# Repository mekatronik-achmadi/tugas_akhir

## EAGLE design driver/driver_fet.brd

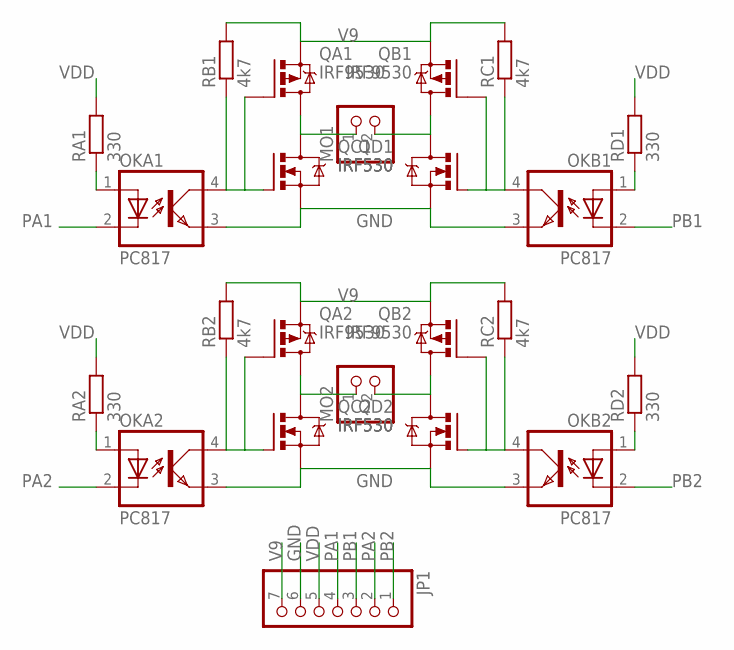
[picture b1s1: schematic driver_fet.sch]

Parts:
JP1: PINHD-1X7; 1X07
MO1, MO2: PINHD-1X2; 1X02
OKA1, OKA2: PC817; DIL04
OKB1, OKB2: PC817; DIL04
QA1, QA2: IRF9530; TO220BV
QB1, QB2: IRF9530; TO220BV
QC1, QC2: IRF530; TO220BV
QD1, QD2: IRF530; TO220BV
RA1, RA2: 330; R1206
RB1, RB2: 4k7; R1206
RC1, RC2: 4k7; R1206
RD1, RD2: 330; R1206

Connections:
GND: JP1.6, OKA1.3 (EMIT), OKA2.3 (EMIT), OKB1.3 (EMIT), OKB2.3 (EMIT), QC1.S, QC2.S, QD1.S, QD2.S
unnamed: MO1.1, QA1.D, QC1.D
unnamed: MO1.2, QB1.D, QD1.D
unnamed: MO2.1, QA2.D, QC2.D
unnamed: MO2.2, QB2.D, QD2.D
unnamed: OKA1.4 (COL), QA1.G, QC1.G, RB1.1
unnamed: OKB1.4 (COL), QB1.G, QD1.G, RC1.1
unnamed: OKA2.4 (COL), QA2.G, QC2.G, RB2.1
unnamed: OKA1.1 (A), RA1.1
unnamed: OKB1.1 (A), RD1.1
unnamed: OKB2.4 (COL), QB2.G, QD2.G, RC2.1
unnamed: OKA2.1 (A), RA2.1
unnamed: OKB2.1 (A), RD2.1
PA1: JP1.4, OKA1.2 (C)
PA2: JP1.2, OKA2.2 (C)
PB1: JP1.3, OKB1.2 (C)
PB2: JP1.1, OKB2.2 (C)
V9: JP1.7, QA1.S, QA2.S, QB1.S, QB2.S, RB1.2, RB2.2, RC1.2, RC2.2
VDD: JP1.5, RA1.2, RA2.2, RD1.2, RD2.2

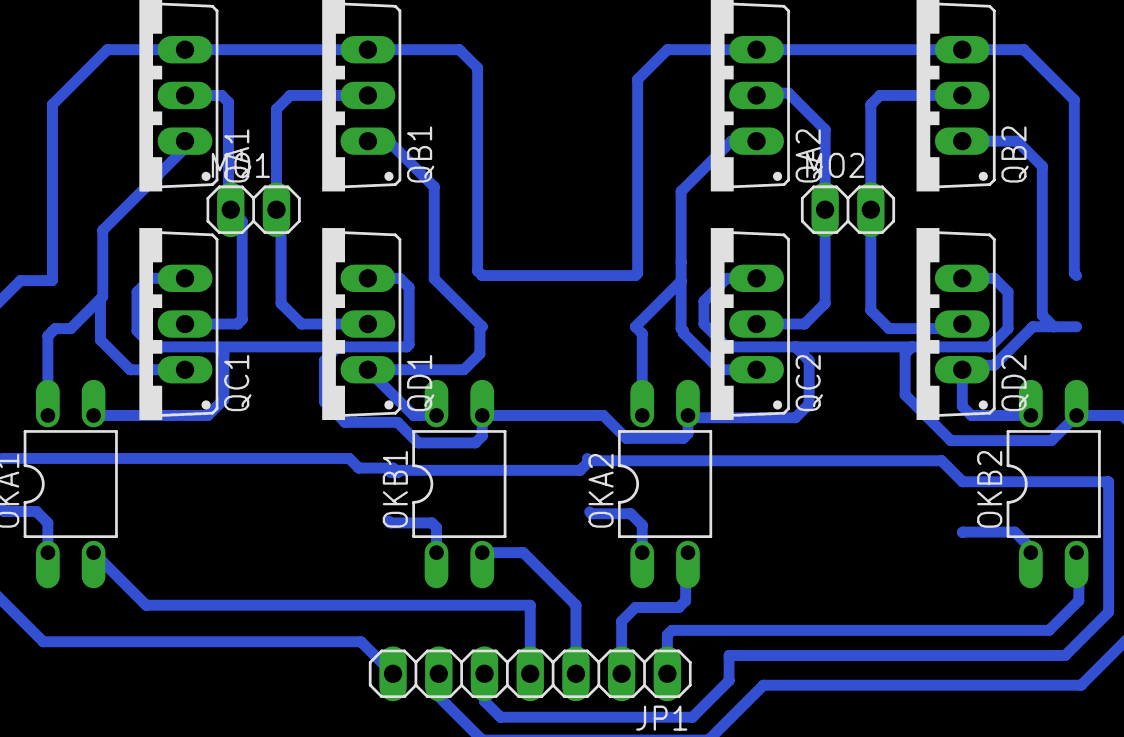
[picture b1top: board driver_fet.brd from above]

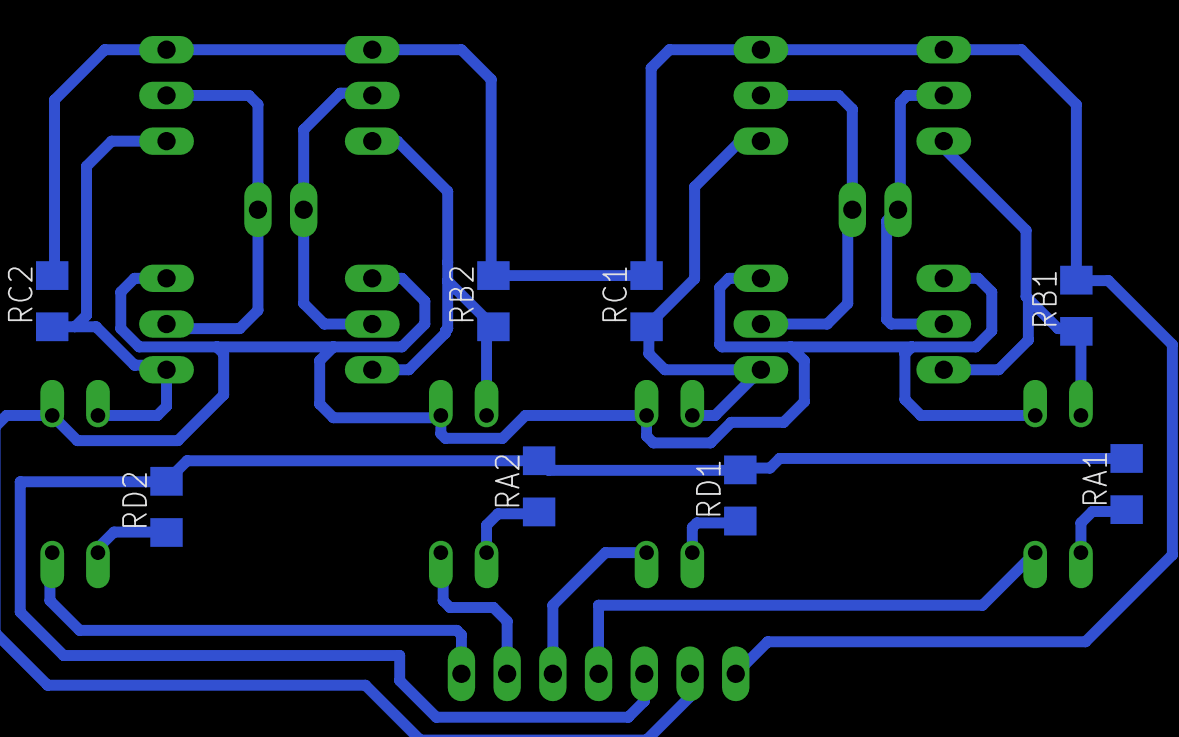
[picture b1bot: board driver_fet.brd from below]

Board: 2 copper layers, 23 parts (8 on the bottom side), 19 nets.

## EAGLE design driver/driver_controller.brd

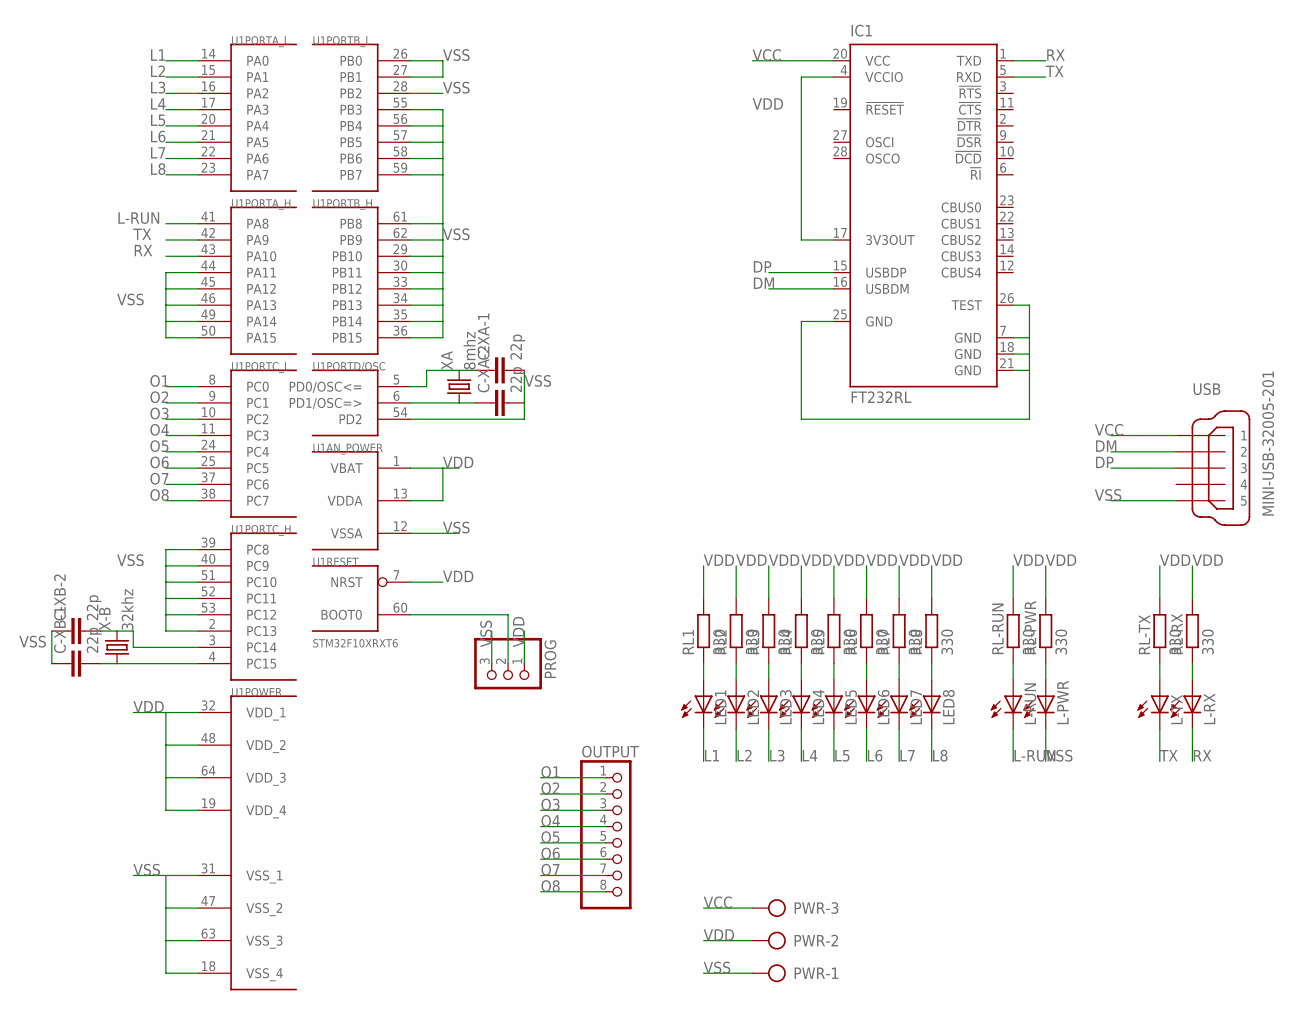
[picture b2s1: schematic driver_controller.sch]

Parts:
C-XA-1, C-XA-2: 22p; C1206
C-XB-1, C-XB-2: 22p; C1206
IC1: FT232RL; SSOP28
L-PWR: LEDSML1206; SML1206
L-RUN: LEDSML1206; SML1206
L-RX: LEDSML1206; SML1206
L-TX: LEDSML1206; SML1206
LED1, LED2, LED3, LED4, LED5, LED6, LED7, LED8: LEDSML1206; SML1206
OUTPUT: PINHD-1X8; 1X08
PROG: PINHD-1X3; 1X03
PWR: AK300/3
RL1, RL2, RL3, RL4, RL5, RL6, RL7, RL8: 330; R1206
RL-PWR: 330; R1206
RL-RUN: 330; R1206
RL-RX: 330; R1206
RL-TX: 330; R1206
U1: STM32F10XRXT6; TQFP64
USB: MINI-USB-32005-201; 32005-201
X-B: 32khz; TC26V
XA: 8mhz; HC49/S

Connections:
DM: IC1.16 (USBDM), USB.2
DP: IC1.15 (USBDP), USB.3
L1: LED1.C, U1.14 (PA0)
L2: LED2.C, U1.15 (PA1)
L3: LED3.C, U1.16 (PA2)
L4: LED4.C, U1.17 (PA3)
L5: LED5.C, U1.20 (PA4)
L6: LED6.C, U1.21 (PA5)
L7: LED7.C, U1.22 (PA6)
L8: LED8.C, U1.23 (PA7)
L-RUN: L-RUN.C, U1.41 (PA8)
unnamed: PROG.2, U1.60 (BOOT0)
unnamed: C-XB-1.2, U1.4 (PC15), X-B.1
unnamed: C-XB-2.2, U1.3 (PC14), X-B.2
unnamed: LED1.A, RL1.1
unnamed: C-XA-2.1, U1.6 (PD1/OSC=>), XA.1
unnamed: C-XA-1.1, U1.5 (PD0/OSC<=), XA.2
unnamed: LED2.A, RL2.1
unnamed: L-PWR.A, RL-PWR.1
unnamed: LED3.A, RL3.1
unnamed: LED4.A, RL4.1
unnamed: LED5.A, RL5.1
unnamed: LED6.A, RL6.1
unnamed: LED7.A, RL7.1
unnamed: LED8.A, RL8.1
unnamed: L-RUN.A, RL-RUN.1
unnamed: L-TX.A, RL-TX.1
unnamed: L-RX.A, RL-RX.1
O1: OUTPUT.1, U1.8 (PC0)
O2: OUTPUT.2, U1.9 (PC1)
O3: OUTPUT.3, U1.10 (PC2)
O4: OUTPUT.4, U1.11 (PC3)
O5: OUTPUT.5, U1.24 (PC4)
O6: OUTPUT.6, U1.25 (PC5)
O7: OUTPUT.7, U1.37 (PC6)
O8: OUTPUT.8, U1.38 (PC7)
RX: IC1.1 (TXD), L-RX.C, U1.43 (PA10)
TX: IC1.5 (RXD), L-TX.C, U1.42 (PA9)
VCC: IC1.20 (VCC), PWR.3, USB.1
VDD: IC1.4 (VCCIO), IC1.17 (3V3OUT), PROG.1, PWR.2, RL1.2, RL2.2, RL3.2, RL4.2, RL5.2, RL6.2, RL7.2, RL8.2, RL-PWR.2, RL-RUN.2, RL-RX.2, RL-TX.2, U1.1 (VBAT), U1.7 (NRST), U1.13 (VDDA), U1.19 (VDD_4), U1.32 (VDD_1), U1.48 (VDD_2), U1.64 (VDD_3)
VSS: C-XA-1.2, C-XA-2.2, C-XB-1.1, C-XB-2.1, IC1.7 (GND), IC1.18 (GND), IC1.21 (GND), IC1.25 (GND), IC1.26 (TEST), L-PWR.C, PROG.3, PWR.1, U1.2 (PC13), U1.12 (VSSA), U1.18 (VSS_4), U1.26 (PB0), U1.27 (PB1), U1.28 (PB2), U1.29 (PB10), U1.30 (PB11), U1.31 (VSS_1), U1.33 (PB12), U1.34 (PB13), U1.35 (PB14), U1.36 (PB15), U1.39 (PC8), U1.40 (PC9), U1.44 (PA11), U1.45 (PA12), U1.46 (PA13), U1.47 (VSS_2), U1.49 (PA14), U1.50 (PA15), U1.51 (PC10), U1.52 (PC11), U1.53 (PC12), U1.54 (PD2), U1.55 (PB3), U1.56 (PB4), U1.57 (PB5), U1.58 (PB6), U1.59 (PB7), U1.61 (PB8), U1.62 (PB9), U1.63 (VSS_3), USB.5

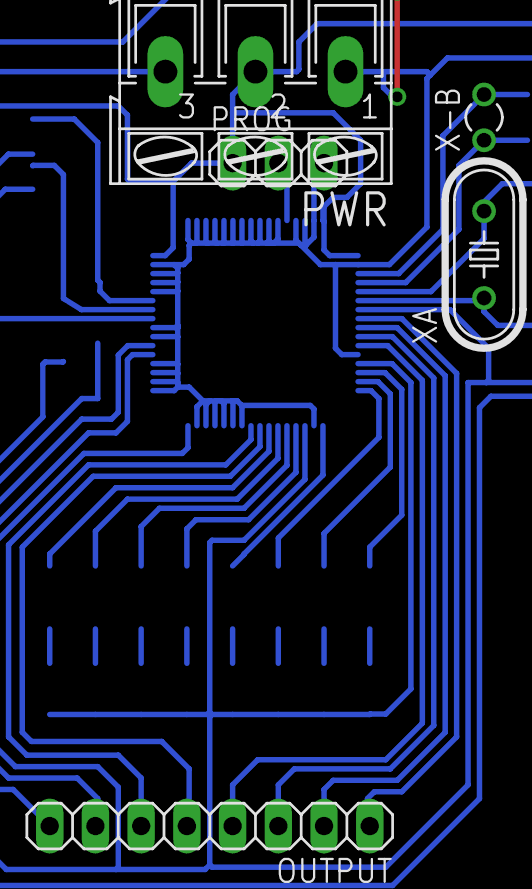
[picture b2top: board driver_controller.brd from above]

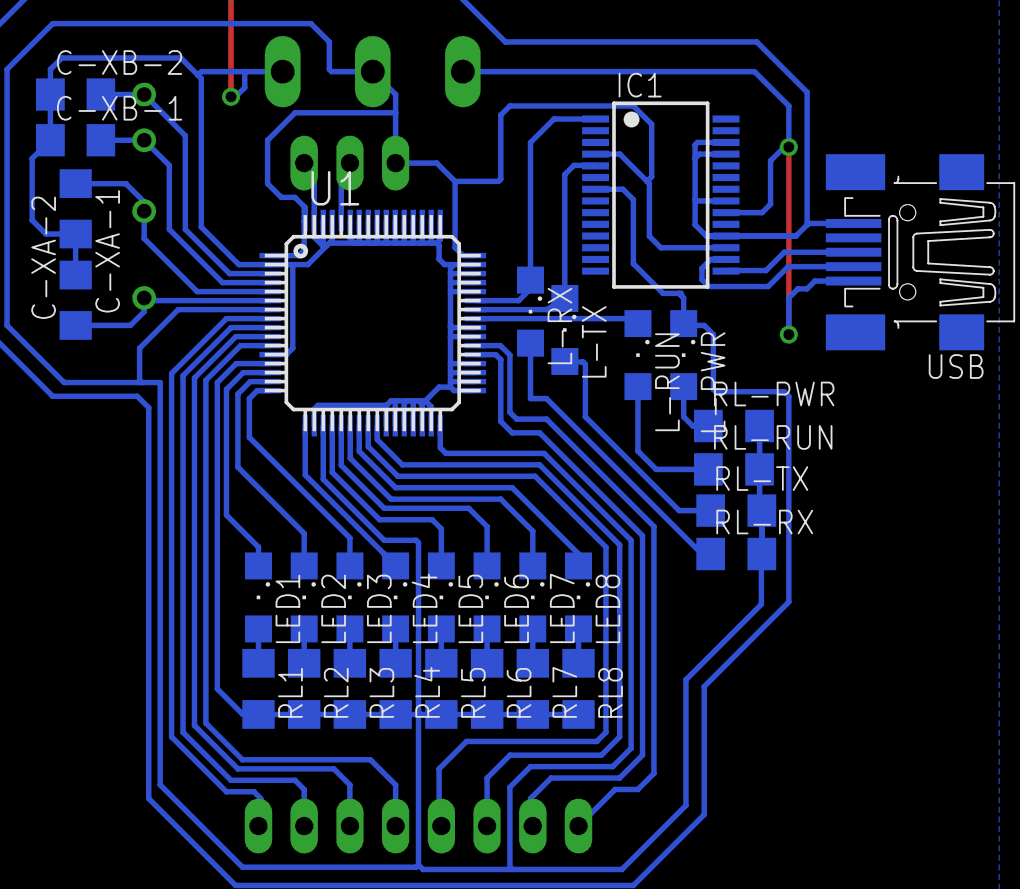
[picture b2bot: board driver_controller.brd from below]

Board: 2 copper layers, 36 parts (31 on the bottom side), 41 nets.

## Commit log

2014-09-22 Proposal
2014-09-22 masih proposal
2014-09-27 Proposal sudah print (lanjutkan)
    board driver contoller and fet
2014-09-28 ganti pake mini USB
2014-10-01 Proposal tinggal tinjauan teori
2014-10-01 proposal tinggal teori dan rancangan color tracking
2014-10-02 draw square boundary
2014-10-02 flowchart color tracking
2014-10-02 Besok ke Pembimbing
2014-10-03 goto pembimbing
2014-10-06 verifikasi proposal
2014-10-20 until RTOS running
2014-10-21 keyboard-override manual control DONE
2014-10-23 manual override
2014-10-27 1st vision and serial integrated
2014-10-27 vision and serial worksa
2014-10-28 seminar proposal
2014-11-05 - Revisi SemPro - Revisi RTOS - Revisi QRobot
2014-11-09 bismillah seminar proposal
2014-11-14 capture test
2014-11-15 some analisis (what?) software
2014-11-16 pixel analisys
2014-11-16 1# percobaan tracking and move
    cukup berhasil
2014-11-17 changes
    1. Sat dan Val range
    2. Minimum dan Maximum Area
2014-11-17 add informational mesage
2014-11-17 info moved on desired range of Area value
2014-11-17 ready to test run 1#
2014-11-17 tinggal smooth kan gerakan
2014-11-23 coba ambil data
2014-11-24 add openfile feature
2014-11-24 add File Open feature
2014-11-24 change standard value
2014-11-24 correct blue color
2014-11-25 software buat analisa data
2014-11-25 fast working
2014-12-05 data jarak
2014-12-12 progres 1
    BUKU !!!!!!!!!!!
2015-01-02 progress 2
2015-01-04 print buat pendaftaran
2015-01-08 Daftar seminar
2015-01-13 persiapan seminar TA
2015-01-13 ppt again
2015-01-13 nambah fitur
2015-01-13 add feature
2015-03-28 poster siap cetak
2015-04-03 poster
2015-05-29 rebuild
2016-08-16 tambah poster jpg
2016-09-12 pdf-ed
2016-09-15 development
